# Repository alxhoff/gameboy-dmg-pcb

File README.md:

# Gameboy DMG Raspberry Pi Board

My revived Corona project, work in progress. The idea of this board is to be a single board drop in for the Gameboy DMG case that is readily availble from all the normal places (eBay, AliExpress etc.) to provide easy game emulation using a Raspberry Pi Zero with distros such as RetroPie. The whole style of the board is that the PCB itself is self explanitory and doesn't require you to go through the schematics, something almost anyone with a bit of soldering knowledge can put together. Many features of the board can be enabled/disabled or changed using the many solder jumper pads.

The board is made in two variants:

- A cheaper to produce <100mm x <100mm board that can be very cheaply produced from manufactureres such as [JLC](https://jlcpcb.com/) and [PCBWay](https://www.pcbway.com).
- A full size (complete case utilization) board that places everything on the same motherboard

# Common components to both implementation

Both boards implement the core required features for creating a portable handheld device. The big difference is that the full size board can make use of the power switches and case cutouts that are more than 100mm from the bottom of the case, as well as being able to place the screen on the motherboard and not require a screen breakout to be used.

## Lipo charger and boost converter

The core component of a handheld device is that is can be battery powered. As such, and to avoid using prefab shields, the board has an onboard Lipo charger and battery protection that then feeds a boost converter to provide the rest of the board with the required 5V to power the RPi, screen and audio.

The Lipo charger is based around a TP4056 charger and a FS312F-G & FS8205 protection IC combo, this feeds the MT3608 boost converter. The board has two through hole battery connections where a standard single cell 4.2v Lipo battery should be connected. The front side of the PCB also has charging status SMD LEDs that can be optionally connected by jumping the appropriate jumper.

## Buttons

The board uses the standard default button layout of the Gameboy DMG also providing eight extra button connections that can be made use of through the through hole connections. The buttons are to connectied to the RPi through an MCP23017 GPIO expander, for which I will write a Linux kernel driver once the hardware is complete, it will be linked here once I am done.

## Audio

The board utilizes the PWM audio output of the RPi, providing both a simple low-pass RC filter as well as a 2.5W mono audio amplifier so that the board can actually produce a decent, and audiable, sound output. A compatible speaker 29mm 0.25W speaker should be attached to the appropriate through hole connectors.

## Screen breakout

The board utilizes the 240 x 320 ILI9341 TFT screens which are a breeze to use with Raspberry Pis through framebuffer copy drivers, such as [this](https://github.com/juj/fbcp-ili9341) one. The smaller board provides a through hole breakout where you can connect, via ribbon cable, the screen's breakout board. I am using a 2.4" screen which requires no modification to the case but larger screens can be placed with minimal modification to the case, these breakouts are available on the larger board, connecting the ribbon cable directly to the board. The larger board uses an elongated footprint to give you complete freedom as to where you solder the board along the horizonal axis.

### Small board

The small PCB provides an exact copy of the pinout found on the common LCD breakout boards such as [3.2" MSP3218](http://www.lcdwiki.com/3.2inch_SPI_Module_ILI9341_SKU:MSP3218), [2.8" MSP2807](http://www.lcdwiki.com/2.8inch_SPI_Module_ILI9341_SKU:MSP2807), [2.4" MSP2402](http://www.lcdwiki.com/2.4inch_SPI_Module_ILI9341_SKU:MSP2402), and [2.2" MSP2202](http://www.lcdwiki.com/2.2inch_SPI_Module_ILI9341_SKU:MSP2202). 

These common breakouts also provide a NPN transisor current driver circuit that allow for PWM control on the backlight. The larger board has this on the motherboard.

| Function        | Header Pin           | 
| ------------- |:-------------:| 
| MISO      | 1 | 
| BACKLIGHT/LED      | 2      |  
| SCK | 3      |   
| MOSI      | 4 |
| DC      | 5 |
| RESET      | 6 |
| CS      | 7 |
| GND      | 8 |
| 3.3V      | 9 |

### Large board

The large board uses a header for the ribbon cable to be connected directly. The pinout is as follows. Also see the [relevant](http://www.lcdwiki.com/res/MSP3218/QD-TFT3202%20specification_v1.1.pdf) datasheets for the pinout

| Function        | Header Pin           | 
| ------------- |:-------------:| 
| GND      | 1 | 
| RESET      | 2      |  
| SCK | 3      |   
| DC      | 4 |
| CS      | 5 |
| MOSI      | 6 |
| MISO      | 7 |
| GND      | 8 |
| 3.3V      | 9 |
| BACKLIGHT LED Anode      | 10 |
| BACKLIGHT LED Cathode      | 11 - 14|

# Small board

The small board must provide headers for items that are found outside of the PCB's bounds, such as power switch, power LED etc. All of the headers should be labelled as to what they do.

There are a number of labeled jumpers that enable/disable functionality of external parts such as disabling the external power switch by bridging the boost supply's outbut stright to the 5V rail.

The following jumpers can be found on the board.

| Name |Reference       | Description           | Default State | Notes & WARNINGS!|
| ------------- |:--------:|-------------|:-------------:| ----- |
| Charging LEDs | JP11 | Enables the two onboard SMD LEDs that provide the status of charging from the TP4056 charger | Open |
| Connect Boost  | JP9 | Connects the battery charger/battery to the boost charger that then supplies the 5V rail | Open |
| Power switch  | JP8 | Shorts out the power switch, making the boost supply and the 5V rail always connected  | Open |
| Volume potentiometer  | JP10 & JP14 | Will fix the audio input to the PAM8302 audio amp to the differential signal between the LP audio filter's output and ground, removing ability to control volume in hardware| Open |
| PAM8302 Supply 3.3V  | JP12 | Allows for the powering of the audio amplifier from 3.3V instead of the default 5V | Open |
| PAM8302 Supply 3.3V  | JP13 | Allows for the disconnecting of the audio amplifier from its default 5V supply | Closed | NEVER should both jumpers be connects and the device powered |
| GPIO Expander I2C  | JP2 - JP4 | The GPIO expander responsible for the onboard Gameboy buttons is by default not attached to the RPi | Open |
| TFT Backlight  | JP6 & JP7 | The backlight for the LCD can be either driven by the GPIO pins (allowing PWM) or from a constant 3.3V rail, By default the screen is driven from the 3.3V rail, thus disabling PWM capabilities of the FB driver | Open & Closer respectivley | Both pins shouldn't be connected at the same time |
| RPi Audio Out  | JP1 | By default the PWM audio output of the PRi's GPIO 13 is not connected to the audio pre-amp, amp and speaker, this must be enabled by the user | Open |

# Large board

todo

## RPi header

The RPi Zero connects directly to the PCB, enough said :P

# TODO

Large board needs to be branched from small board once it is finished

## Small board/both

- Before first fab check micro USB placement.
- Expand board to provide mounting holdes for 2.4" TFT breakout.

## Large board

- Horizontal power switch in to fit the native power switch at the top of the device.
- Horizontal trim pot placement to make use of the existing screen contrast cutout.
- Screen placement to support 2.4", 2.8" and 3.2" screens.

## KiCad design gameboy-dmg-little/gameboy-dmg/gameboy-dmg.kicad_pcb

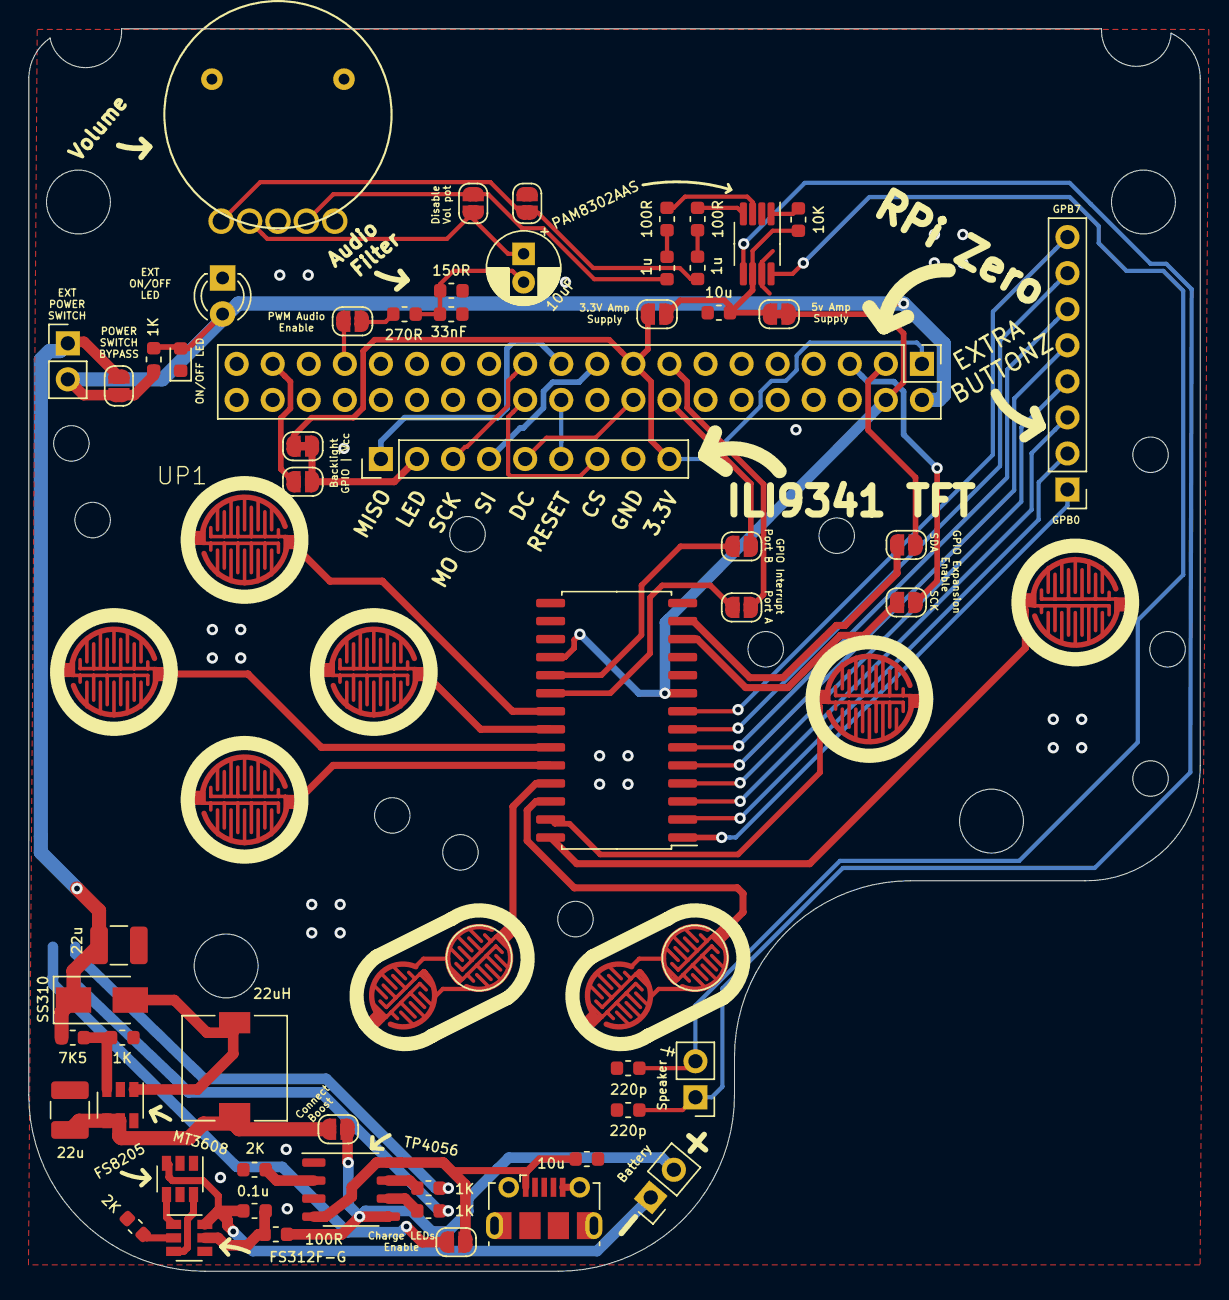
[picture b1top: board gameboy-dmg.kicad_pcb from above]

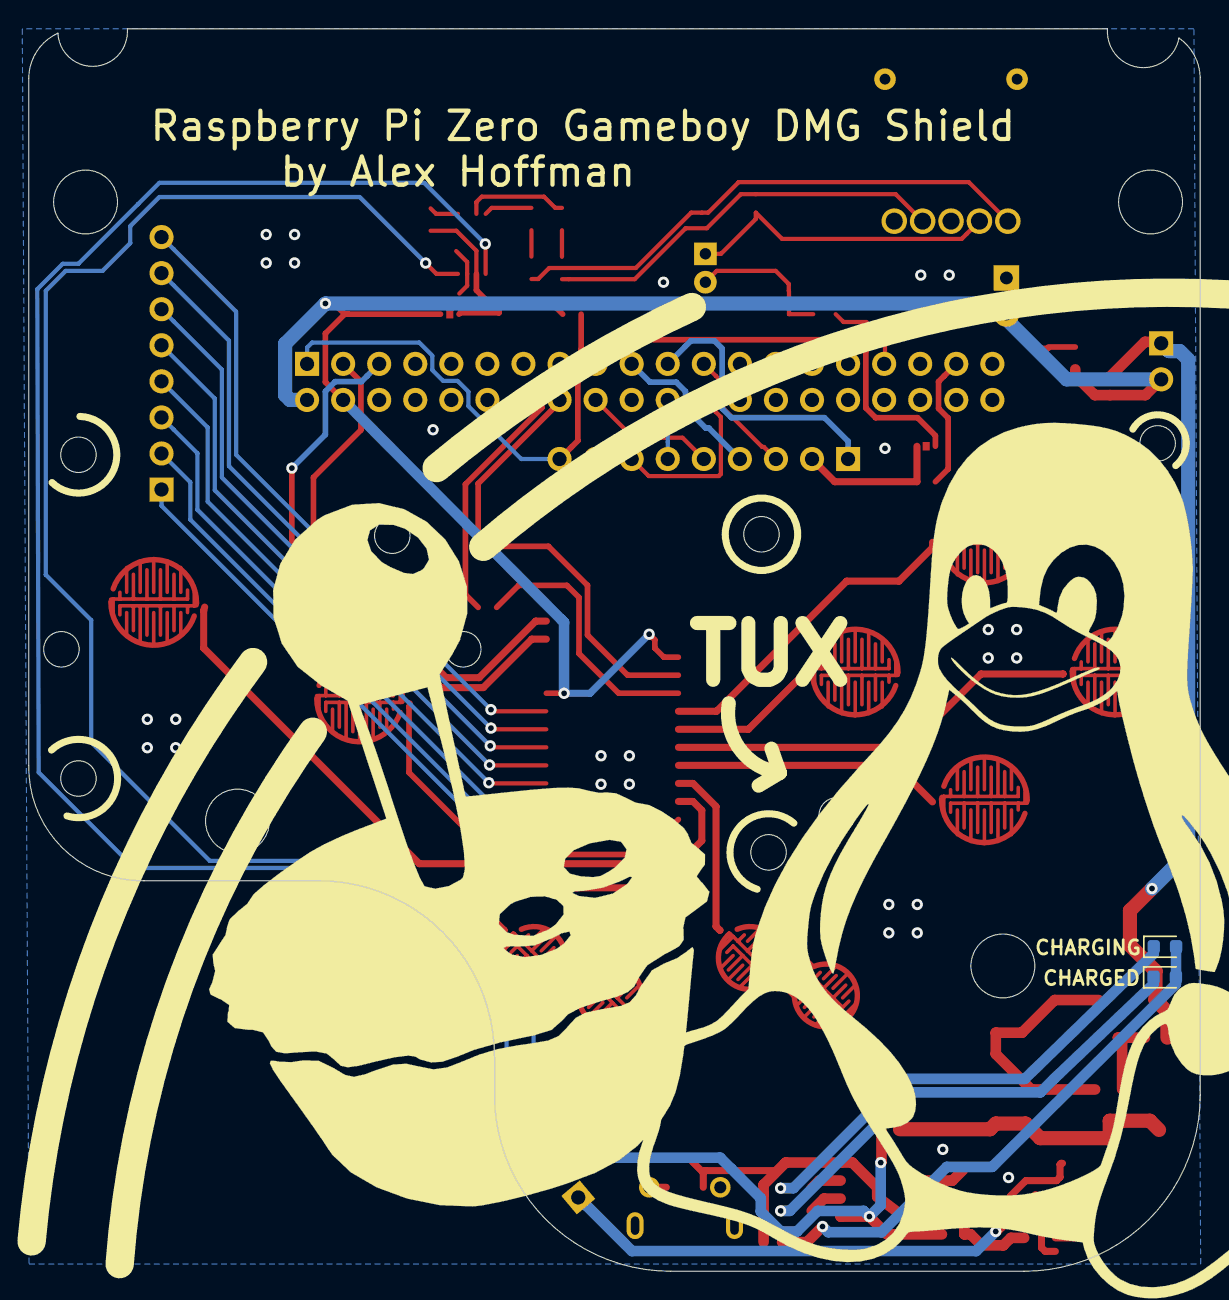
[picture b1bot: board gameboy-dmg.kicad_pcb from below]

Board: 2 copper layers, 82.5 x 87.5 mm, 66 parts (2 on the bottom side), 67 nets.

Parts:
A1: SW_Push; GAMEBOY_BUTTON_PAD-D6MM
B1: SW_Push; GAMEBOY_BUTTON_PAD-D6MM
C1: 33nF; C_0603_1608Metric
C2: 10uF; CP_Radial_D5.0mm_P2.00mm
C3: 0.1u; C_0603_1608Metric
C4, C6: 22u; C_1210_3225Metric
C5, C9: 10u; C_0603_1608Metric
C7, C8: 1u; C_0603_1608Metric
C10, C11: 220p; C_0603_1608Metric
D1, D3, D4: LED; LED_0603_1608Metric
D2: LED; LED_D3.0mm
D5: SS310; D_SMA
DOWN1: SW_Push; GAMEBOY_BUTTON_PAD-D6MM
J1, J8: Conn_01x02; PinHeader_1x02_P2.54mm_Vertical
J3: Conn_01x08; PinHeader_1x08_P2.54mm_Vertical
J5: Raspberry_Pi_2_3; PinHeader_2x20_P2.54mm_Vertical
J6: Conn_01x09; PinHeader_1x09_P2.54mm_Vertical
J7: USB_B_Micro; USB_Micro-B_Molex-105017-0001
JP1, JP2, JP3, JP4, JP5, JP6, JP8, JP9, JP10, JP11, JP12, JP14: SolderJumper_2_Open; SolderJumper-2_P1.3mm_Open_RoundedPad1.0x1.5mm
JP7, JP13: SolderJumper_2_Bridged; SolderJumper-2_P1.3mm_Bridged_RoundedPad1.0x1.5mm
L1: 22uH; L_7.3x7.3_H3.5
LEFT1: SW_Push; GAMEBOY_BUTTON_PAD-D6MM
P1: RK10J_POT; R503_POT
R1, R4, R5, R10: 1K; R_0603_1608Metric
R2: 270R; R_0603_1608Metric
R3: 150R; R_0603_1608Metric
R6, R8: 2K; R_0603_1608Metric
R7, R11, R12: 100R; R_0603_1608Metric
R9: 7K5; R_0603_1608Metric
R13: 10K; R_0603_1608Metric
RIGHT1: SW_Push; GAMEBOY_BUTTON_PAD-D6MM
SELECT1: SW_Push; GAMEBOY_BUTTON_PAD-DUAL_D4MM
START1: SW_Push; GAMEBOY_BUTTON_PAD-DUAL_D4MM
SW1: SW_DIP_x01; PinHeader_1x02_P2.54mm_Vertical
U1: MCP23017_SO; SOIC-28W_7.5x17.9mm_P1.27mm
U2: TP4056; SOP-8_3.9x4.9mm_P1.27mm
U3: FS312F-G; SOT-23-6
U4: FS8205; SOT-23-6
U5: MT3608; SOT-23-6
U6: PAM8302AAS; MSOP-8_3x3mm_P0.65mm
UP1: SW_Push; GAMEBOY_BUTTON_PAD-D6MM

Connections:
+3V3: J5.1, J5.17, J6.9, JP7.1, JP12.2
+5V: J5.2, J5.4, JP8.2, JP13.1, R1.1, SW1.2, U1.9, U1.18
/A: A1.1, U1.28
/B: B1.1, U1.27
/DOWN: DOWN1.1, U1.24
/GPIO_INTA: JP5.2, U1.20
/GPIO_INTA_PI: J5.15, JP5.1
/GPIO_INTB: JP4.2, U1.19
/GPIO_INTB_PI: J5.16, JP4.1
/GPIO_SCK: JP2.2, U1.12
/GPIO_SCK_PI: J5.5, JP2.1
/GPIO_SDA: JP3.2, U1.13
/GPIO_SDA_PI: J5.3, JP3.1
/LEFT: LEFT1.1, U1.23
/PWM_AUDIO_OUT: JP1.2, R2.2
/RIGHT: RIGHT1.1, U1.22
/SELECT: SELECT1.1, U1.25
/START: START1.1, U1.26
/TFT_BACKLIGHT: J6.2, JP6.2, JP7.2
/TFT_BACKLIGHT_GPIO: J5.37, JP6.1
/TFT_CS: J5.24, J6.7
/TFT_DC: J5.18, J6.5
/TFT_MISO: J5.21, J6.1
/TFT_MOSI: J5.19, J6.4
/TFT_RESET: J5.22, J6.6
/TFT_SCK: J5.23, J6.3
/TP4056_LIPO_BOOST/5V_BOOST: C6.1, D5.1, JP8.1, R9.1, SW1.1
/TP4056_LIPO_BOOST/BAT+: J8.2, JP9.1, R7.1, U2.5
/TP4056_LIPO_BOOST/BAT-: C3.2, J8.1, U3.6, U4.3
/UP: U1.21, UP1.1
/audio/Audio_Vdd: C9.1, JP12.1, JP13.2, R13.1, U6.6
GND: A1.2, B1.2, C1.2, C4.2, C5.2, C6.2, C9.2, C10.2, C11.2, D1.1, D2.1, DOWN1.2, J5.6, J5.9, J5.14, J5.20, J5.25, J5.30, J5.34, J5.39, J6.8, J7.5, J7.6, JP14.2, LEFT1.2, R3.1, R6.2, R8.2, R10.2, RIGHT1.2, SELECT1.2, START1.2, U1.10, U1.15, U1.16, U1.17, U2.1, U2.3, U4.1, U5.2, U6.7, UP1.2
unnamed: C1.1, C2.2, R2.1, R3.2
unnamed: C2.1, JP10.2, P1.2
unnamed: C3.1, R7.2, U3.5
unnamed: C4.1, JP9.2, L1.1, U5.4, U5.5
unnamed: C5.1, J7.1, JP11.1, U2.4, U2.8
unnamed: C7.1, JP10.1, P1.4
unnamed: C7.2, R11.2
unnamed: C8.1, R12.1
unnamed: C8.2, JP14.1, P1.1
unnamed: C10.1, J1.1, U6.5
unnamed: C11.1, J1.2, U6.8
unnamed: D1.2, D2.2, R1.2
unnamed: D3.1, R4.1
unnamed: D3.2, D4.2, JP11.2
unnamed: D4.1, R5.2
unnamed: D5.2, L1.2, U5.1
unnamed: J3.1, U1.1
unnamed: J3.2, U1.2
unnamed: J3.3, U1.3
unnamed: J3.4, U1.4
unnamed: J3.5, U1.5
unnamed: J3.6, U1.6
unnamed: J3.7, U1.7
unnamed: J3.8, U1.8
unnamed: J5.33, JP1.1
unnamed: R4.2, U2.6
unnamed: R5.1, U2.7
unnamed: R6.1, U2.2
unnamed: R8.1, U3.2
unnamed: R9.2, R10.1, U5.3
unnamed: R11.1, U6.3
unnamed: R12.2, U6.4
unnamed: R13.2, U6.1
unnamed: U3.1, U4.4
unnamed: U3.3, U4.6

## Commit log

2020-03-27 Initial PCB idea
2020-03-27 Added some graphics and stuffs
2020-03-27 Added some more bits
2020-03-27 Fixed some missing holes
2020-03-28 Rough lipo charger and 5v boost added
2020-03-28 Broke out all of port B to extenal pins from the MSP GPIO expander
2020-03-28 Cleaning up text
2020-03-29 Moved buttons and audio to individual sheets and added audio amp
2020-03-29 Added unroputed and unchecked horizontal vol pot
2020-03-29 README added
2020-03-29 Little board ready for fab
2020-03-29 Little board ready for check and fab
2020-03-30 Added ribbon cable TFT to big and routed it
2020-03-30 Shifter RPi up
2020-03-30 Fixed up little board
2020-03-30 Fixed up big board
2020-03-30 Big board gerbers
2020-03-30 Little board gerbers
2020-03-30 Prototypes 1.0
2020-04-17 Updated PCBs from initial debugging
